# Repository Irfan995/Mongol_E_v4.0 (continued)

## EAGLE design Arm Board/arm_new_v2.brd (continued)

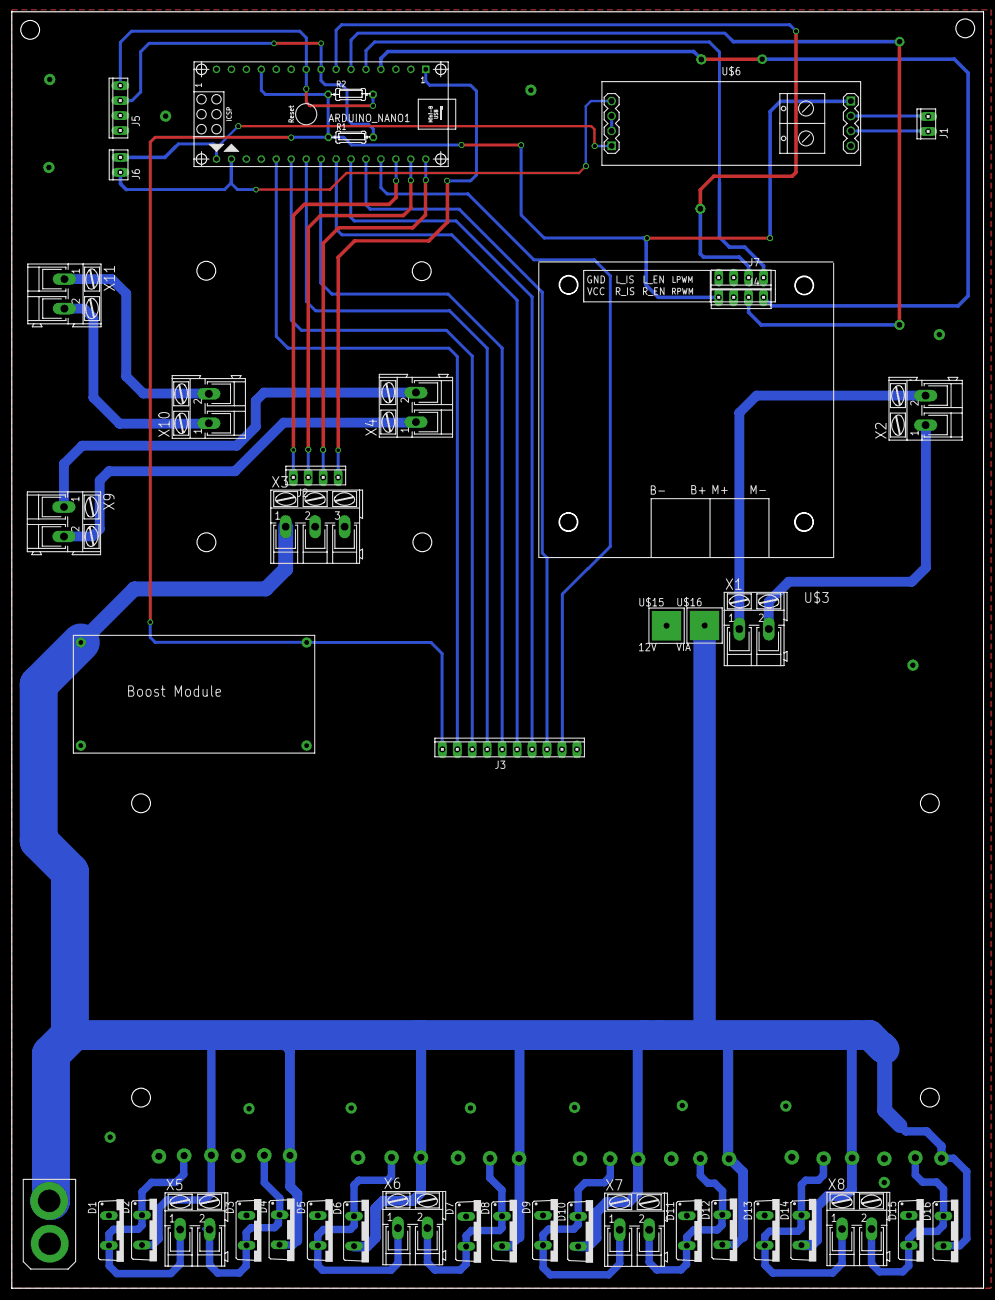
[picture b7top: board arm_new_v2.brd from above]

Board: 2 copper layers, 165.1 x 216.8 mm, 67 parts (0 on the bottom side), 39 nets.

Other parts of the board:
U$3: IBT-2

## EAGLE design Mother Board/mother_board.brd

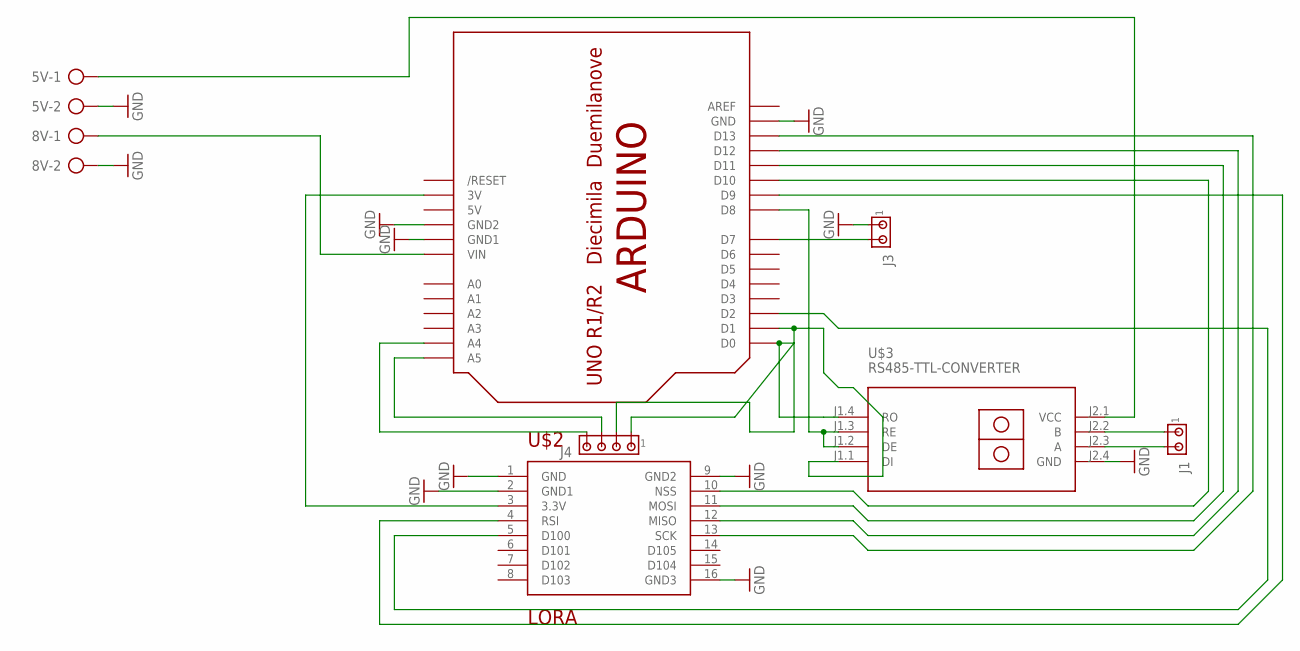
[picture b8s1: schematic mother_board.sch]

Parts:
5V, 8V: AK300/2
J1, J3: MTA02-100; 10X02MTA
J4: MTA04-100; 10X04MTA
U$1: ARDUINOUNO; ARDUINO
U$2: LORA; SX1278
U$3: RS485-TTL-CONVERTER

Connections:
5V: U$1.5V
GND: 5V.2, 8V.2, J3.1, U$1.GND, U$1.GND1, U$1.GND2, U$2.1 (GND), U$2.2 (GND1), U$2.9 (GND2), U$2.16 (GND3), U$3.J2.4 (GND)
unnamed: U$1.3V, U$2.3 (3.3V)
unnamed: 8V.1, U$1.VIN
unnamed: 5V.1, U$3.J2.1 (VCC)
unnamed: J1.2, U$3.J2.3 (A)
unnamed: J1.1, U$3.J2.2 (B)
unnamed: U$1.D8, U$3.J1.2 (DE), U$3.J1.3 (RE)
unnamed: U$1.D10, U$2.10 (NSS)
unnamed: U$1.D11, U$2.11 (MOSI)
unnamed: U$1.D12, U$2.12 (MISO)
unnamed: U$1.D13, U$2.13 (SCK)
unnamed: U$1.D2, U$2.5 (D100)
unnamed: U$1.D9, U$2.4 (RSI)
unnamed: J4.4, U$1.A4
unnamed: J4.3, U$1.A5
unnamed: J4.1, U$1.D0
unnamed: J4.2, U$1.D1, U$3.J1.1 (DI)
unnamed: J3.2, U$1.D7

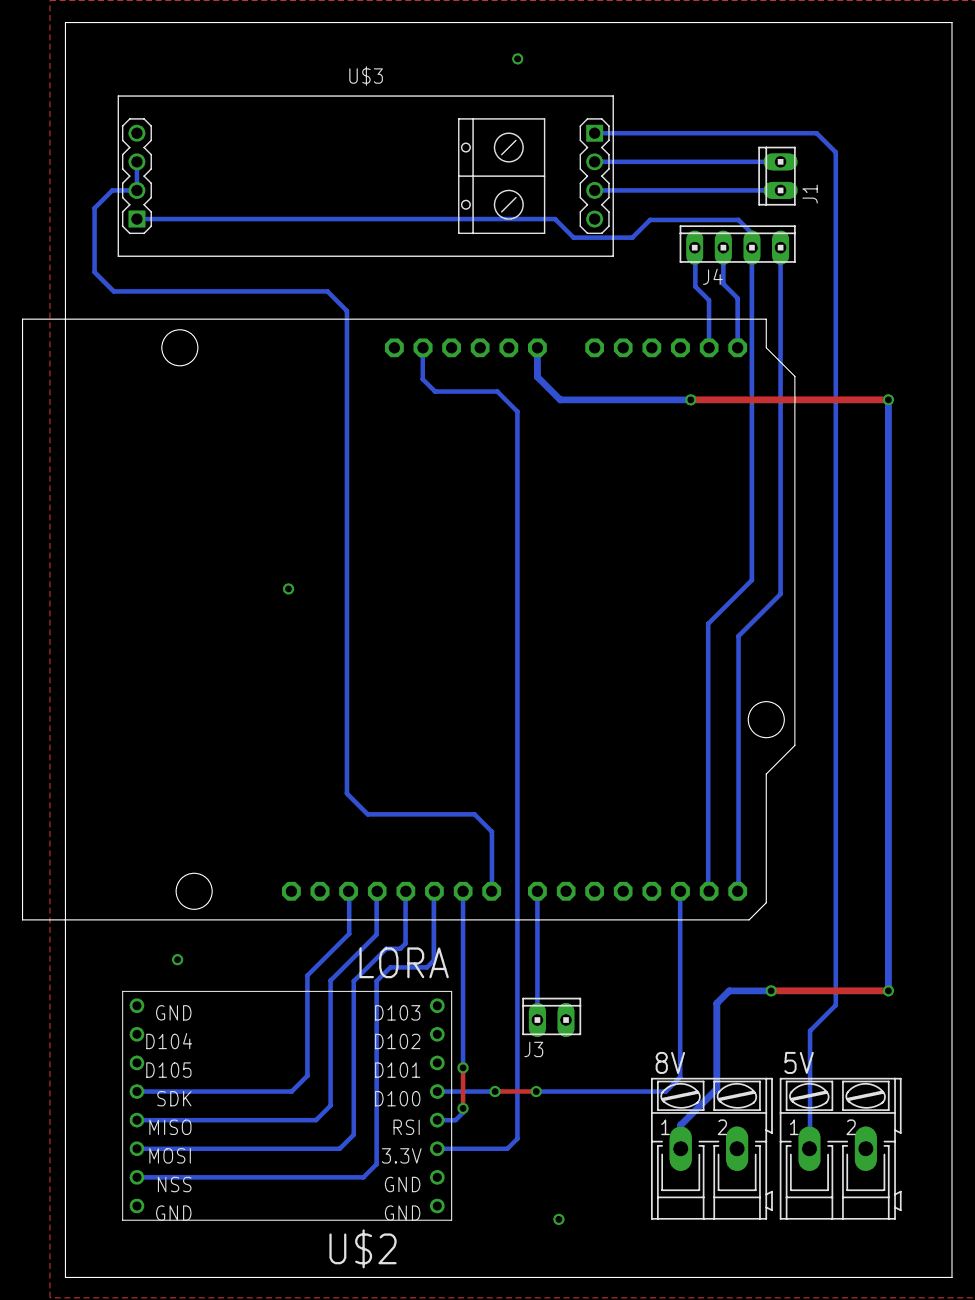
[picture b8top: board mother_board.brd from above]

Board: 2 copper layers, 82.5 x 111.4 mm, 8 parts (1 on the bottom side), 18 nets.

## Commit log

2020-03-21 Added Circuit Designs
